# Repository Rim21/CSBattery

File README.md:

# CSBattery
A battery powered Fan circuit for CSOS

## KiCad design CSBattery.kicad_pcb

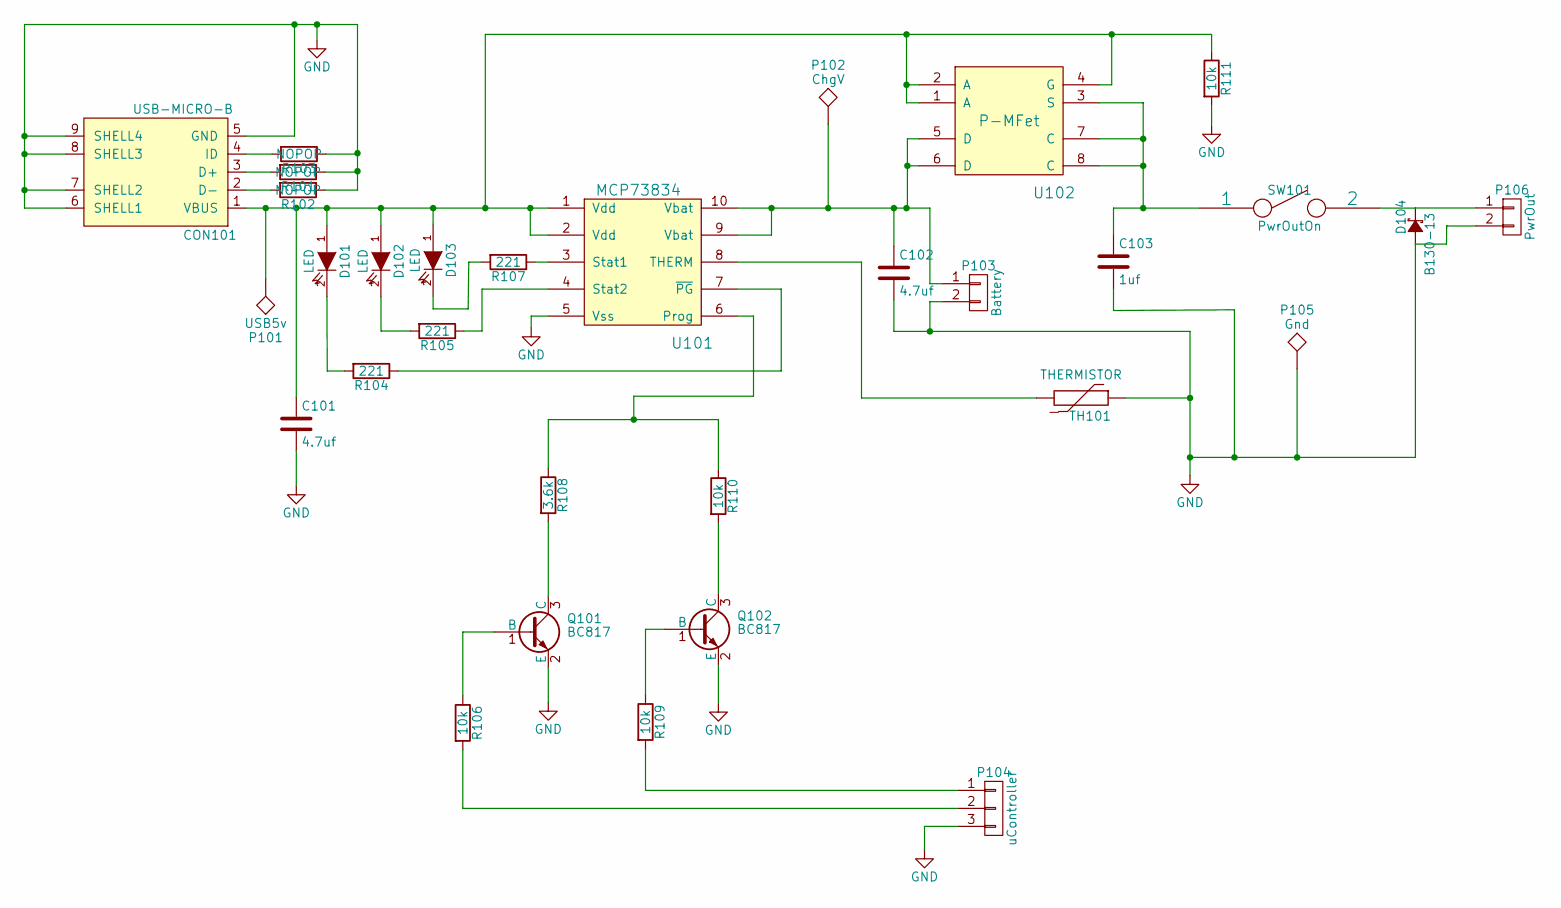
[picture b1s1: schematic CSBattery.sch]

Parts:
C101, C102: 4.7uf; C_0805_HandSoldering
C103: 1uf; C_0805_HandSoldering
CON101: USB-MICRO-B; USB_Micro-B_Custom; MPN 10103594-0001LF
D101: LED; LED-0805; MPN KPHCM-2012EC-T
D102: LED; LED-0805; MPN 5988160107F
D103: LED; LED-0805; MPN OVS-0803
D104: B130-13; Diode-DO-214BA; MPN B130-13-F
P101: USB5v; Measurement_Point_Round-TH_Small
P102: ChgV; Measurement_Point_Round-TH_Small
P103: Battery; Pin_Header_Straight_1x02
P104: uController; Pin_Header_Straight_1x03
P105: Gnd; Measurement_Point_Round-TH_Small
P106: PwrOut; Pin_Header_Straight_1x02
Q101, Q102: BC817; SOT-23; MPN BC817-16_215
R101, R102, R103: NOPOP; R_0805_HandSoldering
R104, R105, R107: 221; R_0805_HandSoldering
R106, R109, R110, R111: 10k; R_0805_HandSoldering
R108: 3.6k; R_0805_HandSoldering
SW101: PwrOutOn; Pin_Header_Straight_1x02
TH101: THERMISTOR; Resistor_Horizontal_RM10mm; MPN NTCLE100E3103JB0
U101: MCP73834; MSOP-10_3x3mm_Pitch0.5mm; MPN MCP73834-FCI/UN
U102: P-MFet; SO-8; MPN FDFS2P753Z

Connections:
GND: C101.2, C102.2, C103.2, CON101.5 (GND), CON101.6 (SHELL1), CON101.7 (SHELL2), CON101.8 (SHELL3), CON101.9 (SHELL4), D104.1 (A), P103.2, P104.3, P105.1, P106.2, Q101.2 (E), Q102.2 (E), R101.1, R102.1, R103.1, R111.2, TH101.1, U101.5 (Vss)
unnamed: C101.1, CON101.1 (VBUS), D101.1 (A), D102.1 (A), D103.1 (A), P101.1, R111.1, U101.1 (Vdd), U101.2 (Vdd), U102.1 (A), U102.2 (A), U102.4 (G)
unnamed: C102.1, P102.1, P103.1, U101.9 (Vbat), U101.10 (Vbat), U102.5 (D), U102.6 (D)
unnamed: C103.1, SW101.1, U102.3 (S), U102.7 (C), U102.8 (C)
unnamed: CON101.2 (D-), R102.2
unnamed: CON101.3 (D+), R101.2
unnamed: CON101.4 (ID), R103.2
unnamed: D101.2 (K), R104.2
unnamed: D102.2 (K), R105.2
unnamed: D103.2 (K), R107.2
unnamed: D104.2 (C), P106.1, SW101.2
unnamed: P104.1, R109.2
unnamed: P104.2, R106.2
unnamed: Q101.1 (B), R106.1
unnamed: Q101.3 (C), R108.2
unnamed: Q102.1 (B), R109.1
unnamed: Q102.3 (C), R110.2
unnamed: R104.1, U101.7 (~PG)
unnamed: R105.1, U101.4 (Stat2)
unnamed: R107.1, U101.3 (Stat1)
unnamed: R108.1, R110.1, U101.6 (Prog)
unnamed: TH101.2, U101.8 (THERM)

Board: 2 copper layers, 31 parts (0 on the bottom side), 22 nets, no tracks yet.

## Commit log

2015-04-22 created schematic symbol for Battery Charger IC
2015-04-22 updated schematic with USB and added a gitignore file
2015-04-22 updated schematic with programmable voltage divider for charge current selection
2015-04-23 updated schematic with power path and uController selectable charge range
2015-04-25 updated part numbers and changed Mosfet and Diode to an all in one package
2015-04-26 assigned footprints, created custom USB footprint and library
2015-04-26 amended schematic to incorporate a gnd reference line for the uController signals
2015-04-28 updated schematic to include a flyback schottky diode to protect the circuit from Fan inductance
